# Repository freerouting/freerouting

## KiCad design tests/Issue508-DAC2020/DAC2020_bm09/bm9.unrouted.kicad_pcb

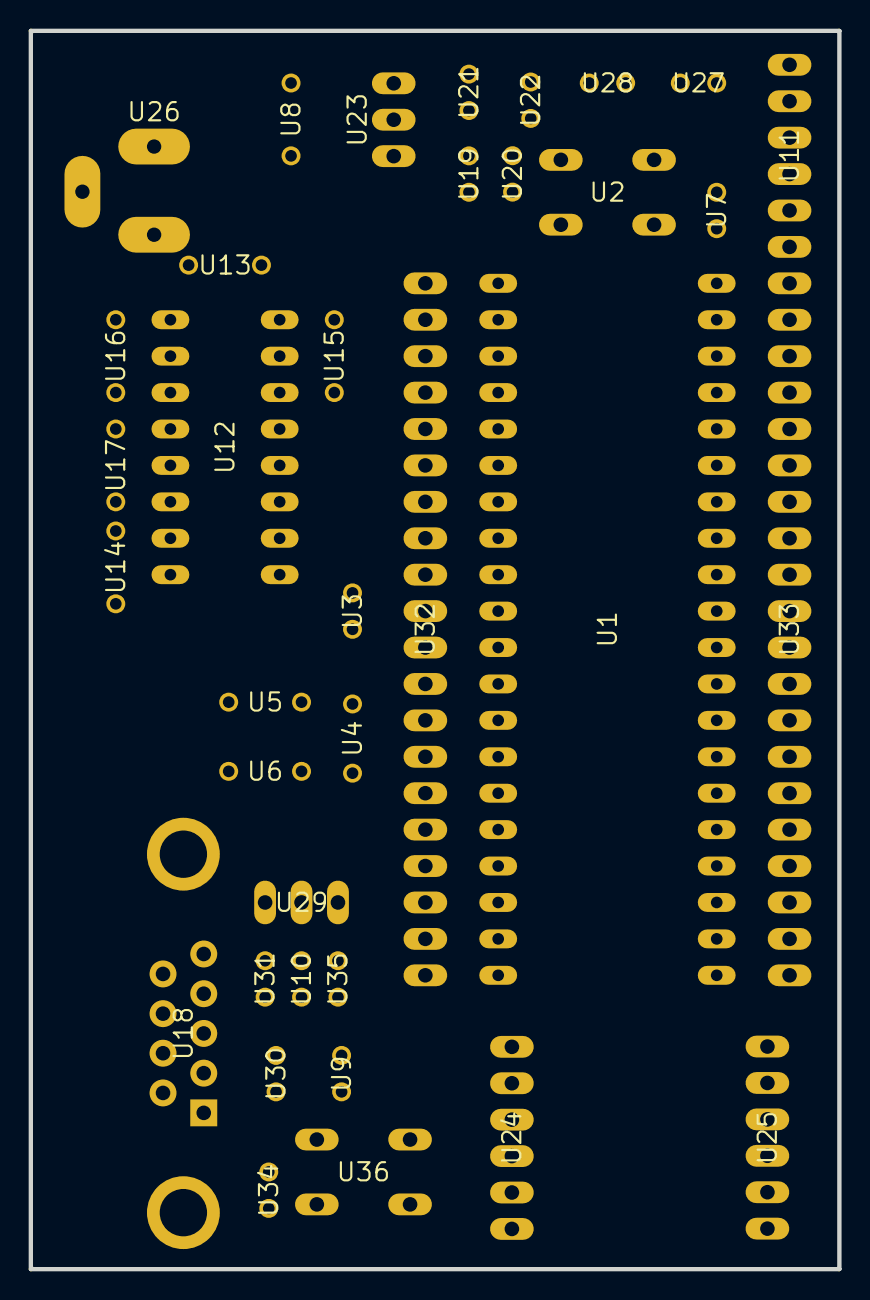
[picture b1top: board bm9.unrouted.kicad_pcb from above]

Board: 16 copper layers, 56.4 x 86.4 mm, 36 parts (0 on the bottom side), 58 nets, no tracks yet.

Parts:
U1: DIL40
U2, U36: B3F-10XX
U3, U22: C025-024X044
U4: HC49_S
U5, U6, U13, U14, U15, U16, U17: C050-024X044
U7, U10, U19, U20, U21, U28, U31, U34, U35: V526-0
U8: C050-025X075
U9, U27, U30: LED3MM
U11, U24, U25: 1X06
U12: DIL16
U18: DB9
U23: 317TS
U26: 733980-62
U29: MA03-1
U32, U33: MA20-1

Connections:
/3.3V_SRC: U1.11, U1.32, U3.1, U7.1, U11.2, U12.16, U13.2, U15.1, U21.2, U22.1, U23.2, U24.3, U28.1, U32.10, U33.9, U36.1
/MRF_CS: U1.17, U24.5, U32.4
/MRF_INT: U1.34, U25.3, U33.7
/MRF_RESET: U1.15, U25.5, U32.6
/MRF_SCK: U1.18, U25.1, U32.3
/MRF_SDI: U1.23, U24.6, U33.18
/MRF_SDO: U1.24, U25.2, U33.17
/MRF_WAKE: U1.16, U25.4, U32.5
/N$17: U1.26, U12.9, U33.15
/N$21: U1.25, U12.10, U33.16
/OS1: U1.13, U4.1, U5.1, U32.8
/OSC2: U1.14, U4.2, U6.1, U32.7
GND: U1.12, U1.31, U2.1, U3.2, U5.2, U6.2, U8.2, U9.K, U11.3, U12.15, U14.1, U15.2, U18.5, U20.1, U22.2, U24.1, U24.2, U25.6, U26.1, U27.K, U30.K, U32.9, U33.10, U34.2
unnamed: U12.2, U13.1
unnamed: U12.6, U14.2
unnamed: U12.1, U16.1
unnamed: U12.3, U16.2
unnamed: U12.4, U17.1
unnamed: U12.5, U17.2
unnamed: U8.1, U23.3, U26.2
unnamed: U12.7, U18.2
unnamed: U12.8, U18.3
unnamed: U1.1, U2.3, U7.2, U11.1, U32.20
unnamed: U1.2, U32.19
unnamed: U1.3, U32.18
unnamed: U1.4, U32.17
unnamed: U1.5, U32.16
unnamed: U1.6, U32.15
unnamed: U1.7, U32.14
unnamed: U1.8, U32.13
unnamed: U1.9, U32.12
unnamed: U1.10, U32.11
unnamed: U1.19, U32.2
unnamed: U1.20, U32.1
unnamed: U1.21, U33.20
unnamed: U1.22, U33.19
unnamed: U1.27, U33.14
unnamed: U1.28, U33.13
unnamed: U1.29, U33.12
unnamed: U1.30, U33.11
unnamed: U1.33, U33.8
unnamed: U1.35, U33.6
unnamed: U1.36, U33.5
unnamed: U1.37, U33.4
unnamed: U1.38, U33.3
unnamed: U1.39, U11.5, U33.2
unnamed: U1.40, U11.4, U33.1
unnamed: U19.2, U21.1, U23.1
unnamed: U27.A, U28.2
unnamed: U30.A, U31.2
unnamed: U9.A, U10.2
unnamed: U34.1, U35.2, U36.3
unnamed: U29.3, U35.1
unnamed: U10.1, U29.2
unnamed: U29.1, U31.1
unnamed: U19.1, U20.2
unnamed: U18.1, U18.4, U18.6
unnamed: U18.7, U18.8

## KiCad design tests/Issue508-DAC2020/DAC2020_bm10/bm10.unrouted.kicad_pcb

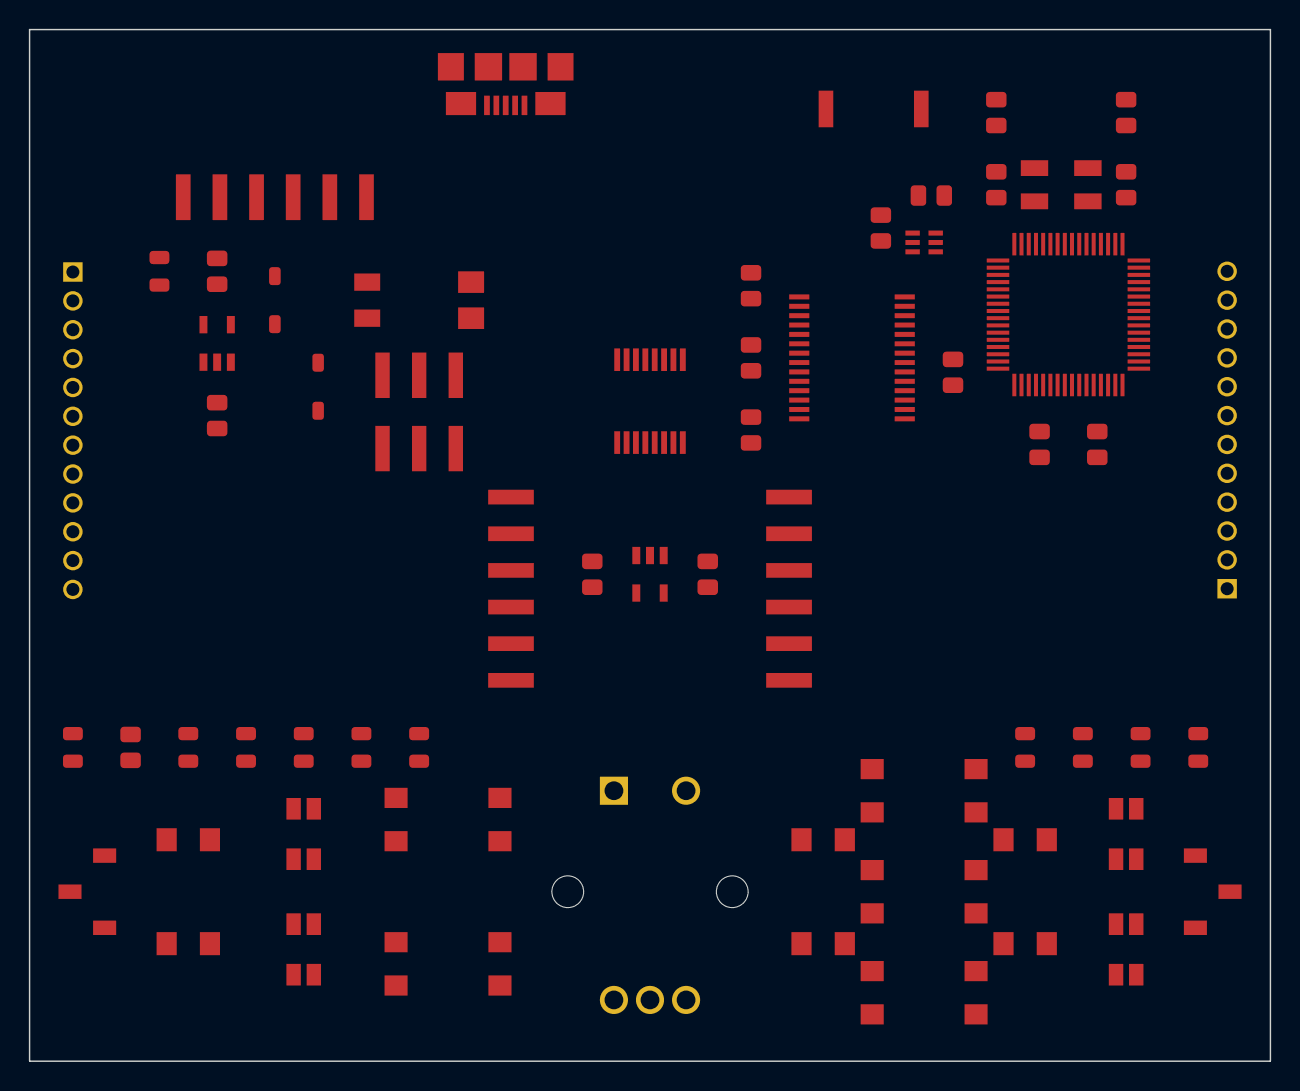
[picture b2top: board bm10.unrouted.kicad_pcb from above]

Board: 4 copper layers, 86.0 x 71.5 mm, 61 parts (0 on the bottom side), 63 nets, no tracks yet.

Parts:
A1: ANTENNA-CHIP; ANT-2.4GHZ-6.5X2.2MM
B1, B4, B5, B6, B7, B8, B9, B10: PUSHBUTTON_-4.5X4.5; 4.5MM_TACTILE_SWITCH_TL3305AF160QG
B2: BALUN0805; BALUN
B3: BATTERY-SPRING-SMD; WIRE-TERMINAL-1X2-2.5MM-SMD-AVX-009276002021106
C1, C8, C9: 0.1uF; CAPC2012X140_HS
C2: 0.75pF; CAPC2012X140_HS
C3: 22pF; CAPC2012X140_HS
C4, C10, C11, C12, C13, C16, C17: 1uF; CAPC2012X140_HS
C5, C6, C7: 10uF; CAPC2012X140_HS
C14, C15: 12pF; CAPC2012X140_HS
D1, D4, D5, D6: LED-2X-GREEN_RED; LED-2X-LTST-C155
D2, D3: 360mV; SOD3716X135_HS
E1: ROTARY-ENCODER-W_BUTTON-BOURNS-PEC12R-4217F; BOURNS-PEC12R
J1: USB-MICROA-AMPHENOL-10118192-0001LF; USB-MICROA-10118192-0001LF
J2, J3: 2.4K; JST-13-PTH
J4: AVR_SPI_PRG_6-SMD; 2X3-SMD
J7, J8: FRSKY-GIMBAL-2X-SERVO-SMD; 2X-SERVO-SMD
JP1: FTDI_BASIC-SMD; FTDI-BASIC-SMD
R1, R3, R13, R14, R15, R16, R17, R18: 510; RESC2012X60_HS
R2: 10K; RESC2012X60_HS
R7: 2.2K; RESC2012X60_HS
R8: 1.2K; RESC2012X60_HS
S1, S2: POWER-SWITCH-MFS201N-9-Z-SMD-VERTICAL; JS102011JCQN
U1: 3.3V; SOT23-DBV
U2: MCP73831T-2ACI/OT; SOT23-5
U3: FT232RLSSOP; SSOP28DB
U4: ATMEGA128RFA1; QFN-64
U5: DPDT-X2; SOP65P640X110-16
Y1: CRYSTAL5X3; CRYSTAL-SMD-5X3

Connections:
3V3: C12.1, C16.1, C17.1, D4.A2, J4.2, JP1.VCC, R2.2, R8.2, R13.2, R14.2, S2.1, U1.5, U4.23, U4.34, U4.44, U4.54, U4.59, U5.16
/BTN1/SCL: B4.3, B4.4, U4.25
/BTN2/SDA: B5.3, B5.4, U4.26
/BTN_CENTER: B9.1, B9.2, U4.53
/BTN_DOWN: B10.1, B10.2, U4.28
/BTN_LEFT: B7.1, B7.2, U4.51
/BTN_RIGHT: B8.1, B8.2, U4.52
/BTN_UP: B6.1, B6.2, U4.50
/CTS: U3.11, U5.2
/CTS-1: JP1.CTS, U5.1
/DTR: U3.2, U5.14
/DTR-0: C1.2, U5.15
/DTR-1: JP1.DTR, U5.13
/E1-A: E1.A, U4.40
/E1-B: E1.B, U4.41
/E1-BUT: E1.BUTA, U4.27
/FTDI_OUT: C4.2, C9.1, U3.4, U3.17
/GREF: J2.1, J2.4, J3.1, J3.4, J7.1, J7.4, J8.1, J8.4, R8.1
/MISO: J4.1, U4.39
/MOSI: J4.4, U4.38
/PITCH: J3.V, J8.V, U4.2
/RESET: B1.1, B1.2, C1.1, J4.5, R2.1, U4.12
/RF: D4.A1, U4.16
/ROLL: J3.H, J8.H, U4.1
/RXI: U3.5, U5.10
/RXI-0: U4.47, U5.11
/RXI-1: JP1.RXI, U5.9
/RXLED: D5.C2, U3.22
/SCK: J4.3, U4.37
/THROTTLE: J2.V, J7.V, U4.64
/TXLED: D5.C1, U3.23
/TXO: U3.1, U5.6
/TXO-0: U4.46, U5.7
/TXO-1: JP1.TXO, U5.5
/USB_D_N: J1.2, U3.16
/USB_D_P: J1.3, U3.15
/VBUS: C5.1, D1.A2, D2.A, J1.1, U2.4
/VREG_IN: C7.1, C8.1, C10.1, S1.1, U1.1, U1.3, U3.20
/YAW: J2.H, J7.H, U4.63
GND: B1.3, B1.4, B2.5, B3.2A, B3.2B, B4.1, B4.2, B5.1, B5.2, B6.3, B6.4, B7.3, B7.4, B8.3, B8.4, B9.3, B9.4, B10.3, B10.4, C2.2, C3.1, C4.1, C5.2, C6.2, C7.2, C8.2, C9.2, C10.2, C11.2, C12.2, C13.2, C14.2, C15.2, C16.2, C17.2, D1.C1, E1.BUTB, E1.C, J1.5, J1.6, J1.7, J1.8, J1.9, J1.10, J1.11, J2.3, J2.6, J3.3, J3.6, J4.6, J7.3, J7.6, J8.3, J8.6, JP1.GND, R7.2, R15.1, R16.1, R17.1, R18.1, S2.3, U1.2, U2.2, U3.7, U3.18, U3.21, U3.25, U3.26, U4.7, U4.10, U4.11, U4.20, U4.24, U4.33, U4.35, U4.45, U4.55, U4.58, U4.61, U5.8
unnamed: A1.FEED, B2.1, C2.1
unnamed: B2.2, C3.2
unnamed: B2.3, U4.9
unnamed: B2.4, U4.8
unnamed: B3.1A, B3.1B, C6.1, D3.A, U2.3
unnamed: C11.1, U4.21, U4.22
unnamed: C13.1, U4.60
unnamed: C14.1, U4.57, Y1.3
unnamed: C15.1, U4.56, Y1.1
unnamed: D1.A1, R3.1
unnamed: D1.C2, R1.1
unnamed: D4.C1, R15.2
unnamed: D4.C2, R16.2
unnamed: D5.A1, R14.1
unnamed: D5.A2, R13.1
unnamed: D6.A1, U4.15
unnamed: D6.A2, U4.14
unnamed: D6.C1, R18.2
unnamed: D6.C2, R17.2
unnamed: R1.2, R3.2, U2.1
unnamed: R7.1, U2.5
unnamed: S2.2, U5.4, U5.12
VBAT: D2.C, D3.C, S1.2

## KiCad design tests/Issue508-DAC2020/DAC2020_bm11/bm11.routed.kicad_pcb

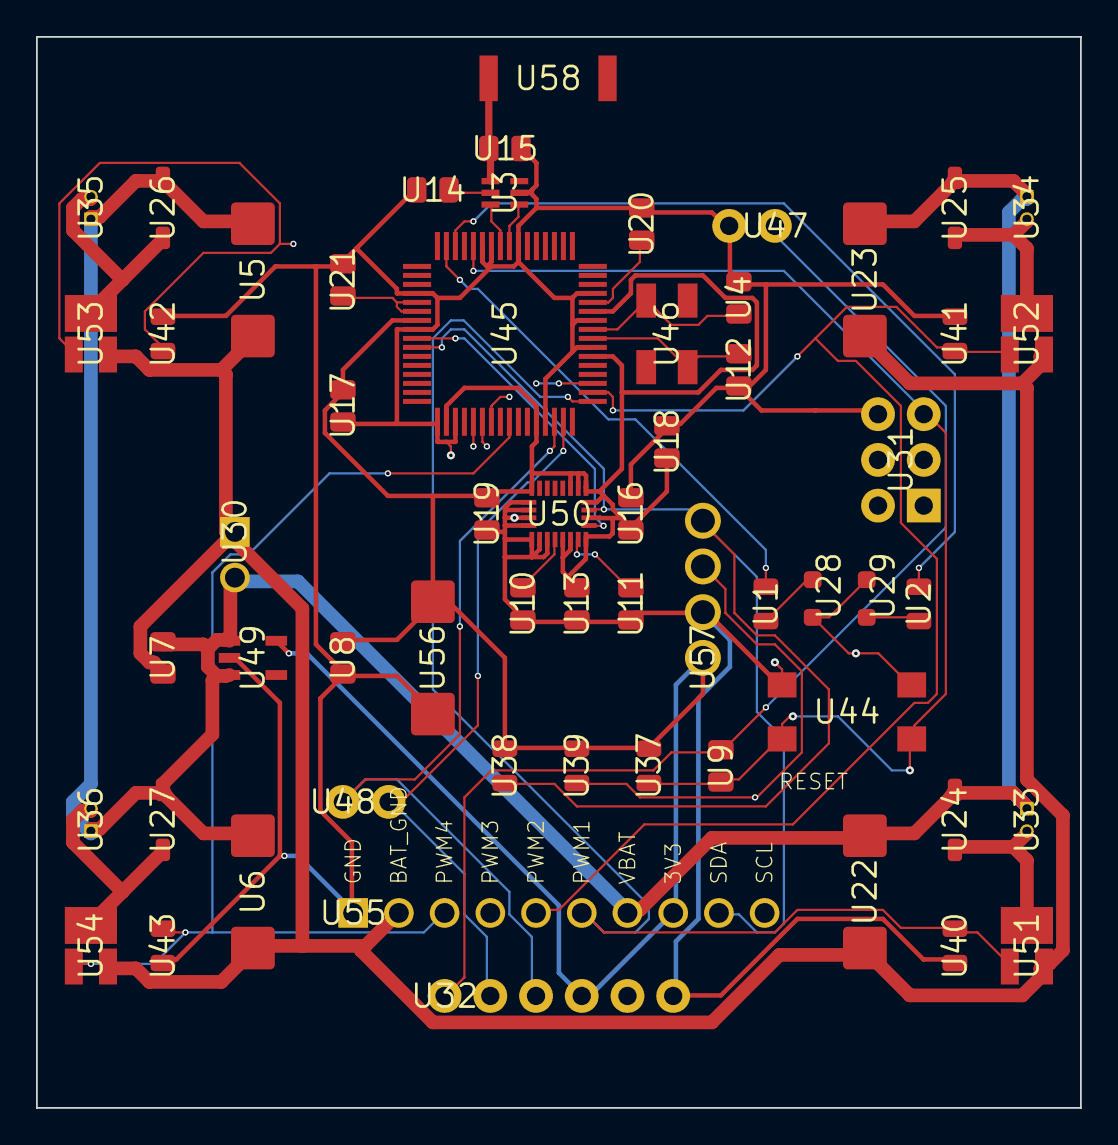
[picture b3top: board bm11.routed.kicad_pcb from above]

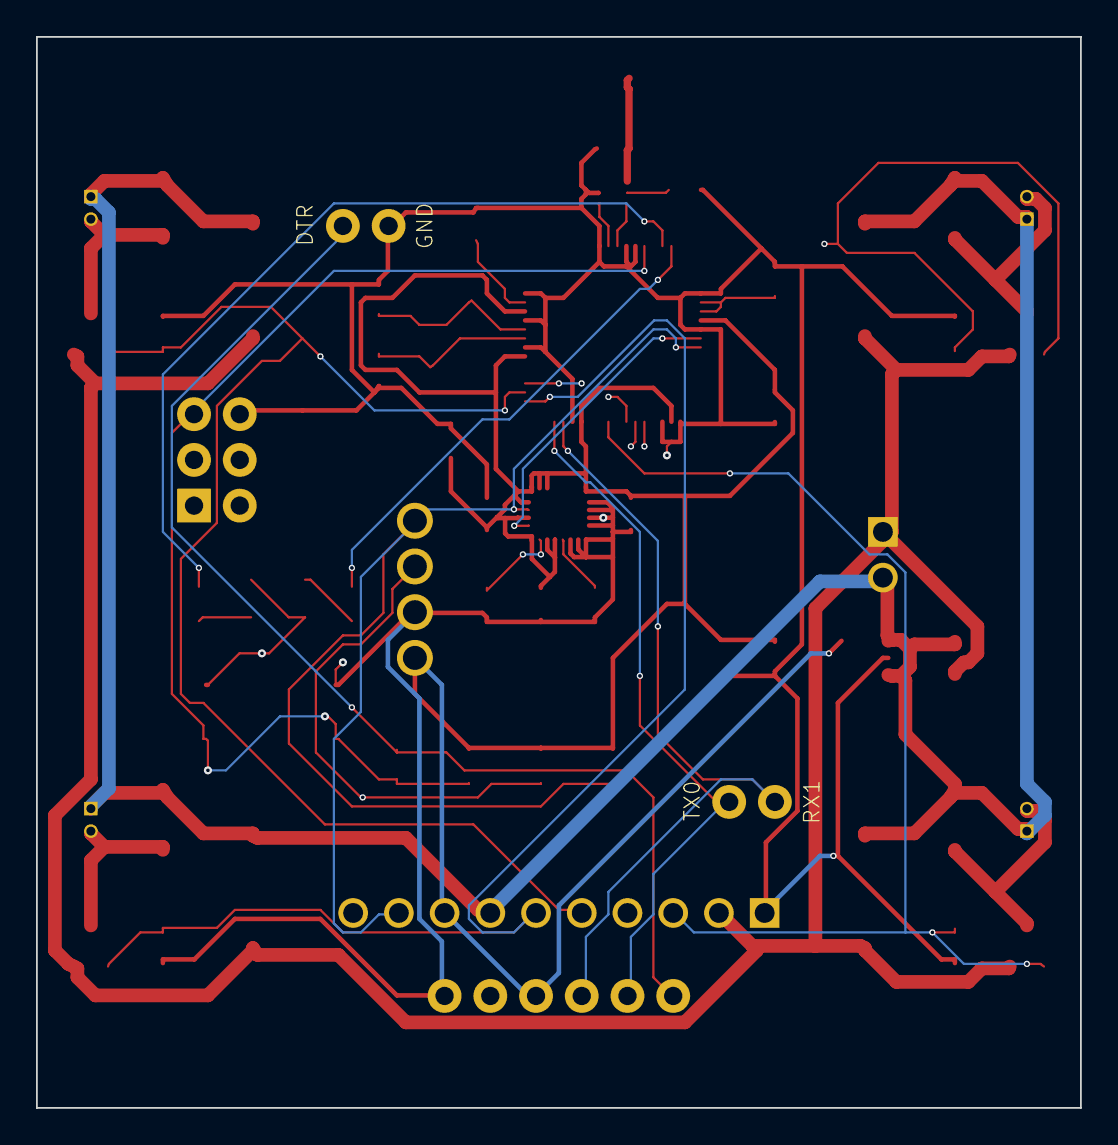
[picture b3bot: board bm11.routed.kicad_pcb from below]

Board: 4 copper layers, 58.0 x 59.5 mm, 58 parts (2 on the bottom side), 35 nets.

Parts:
U1, U2, U37, U38, U39, U40, U41, U42, U43: RESC2012X60_HS
U3: BALUN
U4, U7, U8, U9, U10, U11, U12, U13, U14, U15, U16, U17, U18, U19, U20, U21: CAPC2012X140_HS
U5, U6, U22, U23, U56: CAPMP7343X310_HS
U24, U25, U26, U27: SOD3716X135_HS
U28, U29: LEDSC125X200X120-2_HS
U30: MALE_HEADER_2X1_0.1IN
U31: 2X3-NS
U32: FTDI_BASIC
U33, U34, U35, U36: MOLEX-0530470210
U44: 4.5MM_TACTILE_SWITCH_TL3305AF160QG
U45: QFN-64
U46: CRYSTAL-SMD-5X3
U47: FTDI_BASIC_2PIN_2
U48: FTDI_BASIC_2PIN_1
U49: SOT23-DBV
U50: NEW_IMU_MEDIUM
U51, U52, U53, U54: N_FET_SI2302CDS-T1-E3CT-ND
U55: HDRV10W63P254_10X1_2540X254H838_HS
U57: HDRVR4W80P254_1X4_1066X254X850B
U58: ANT-2.4GHZ-6.5X2.2MM

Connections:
3V3: U8.1, U13.1, U16.1, U17.1, U18.1, U19.1, U32.VCC, U37.2, U38.2, U39.2, U45.23, U45.34, U45.44, U45.54, U45.59, U49.5, U50.CS_A/G, U50.CS_M, U50.DEN_A/G, U50.SDO_A/G, U50.SDO_M, U50.VDD1, U50.VDD2, U50.VDDIO, U50.VDDIO2, U55.8, U56.1, U57.1
/DTR: U9.1, U32.DTR, U47.DTR
/LED1: U2.2, U45.14
/LED2: U1.2, U45.15
/MISO: U31.1, U45.39
/MOSI: U31.4, U45.38
/PWM1: U40.1, U45.49, U51.G, U55.6
/PWM2: U41.1, U45.50, U52.G, U55.5
/PWM3: U42.1, U45.51, U53.G, U55.4
/PWM4: U43.1, U45.41, U54.G, U55.3
/RESET: U9.2, U31.5, U37.1, U44.3, U44.4, U45.12
/RX0: U32.TXO, U45.46, U48.TXO
/SCK: U31.3, U45.37
/SCL: U39.1, U45.25, U50.SCL/SPC, U55.10, U57.3
/SDA: U38.1, U45.26, U50.SDA/SDI/SDO, U55.9, U57.4
/TX0: U32.RXI, U45.47, U48.RXI
BAT_GND: U5.2, U6.2, U7.2, U22.2, U23.2, U30.1, U51.S, U52.S, U53.S, U54.S, U55.2
GND: U3.5, U4.2, U8.2, U10.2, U11.2, U12.2, U13.2, U14.2, U15.2, U16.2, U17.2, U18.2, U19.2, U20.2, U21.2, U28.2, U29.1, U31.6, U32.GND, U40.2, U41.2, U42.2, U43.2, U44.1, U44.2, U45.7, U45.10, U45.11, U45.20, U45.24, U45.33, U45.35, U45.45, U45.55, U45.58, U45.61, U47.CTS, U49.2, U50.GND1, U50.GND2, U50.RES1, U50.RES2, U50.RES3, U50.RES4, U50.RES5, U55.1, U56.2, U57.2
unnamed: U3.1, U15.1, U58.FEED
unnamed: U3.2, U14.1
unnamed: U3.3, U45.9
unnamed: U3.4, U45.8
unnamed: U4.1, U45.57, U46.1
unnamed: U12.1, U45.56, U46.3
unnamed: U20.1, U45.60
unnamed: U21.1, U45.21, U45.22
unnamed: U10.1, U50.CAP
unnamed: U11.1, U50.C1
unnamed: U24.A, U33.2, U51.D
unnamed: U25.A, U34.2, U52.D
unnamed: U26.A, U35.2, U53.D
unnamed: U27.A, U36.2, U54.D
unnamed: U1.1, U28.1
unnamed: U2.1, U29.2
VBAT: U5.1, U6.1, U7.1, U22.1, U23.1, U24.C, U25.C, U26.C, U27.C, U30.2, U33.1, U34.1, U35.1, U36.1, U49.1, U49.3, U55.7

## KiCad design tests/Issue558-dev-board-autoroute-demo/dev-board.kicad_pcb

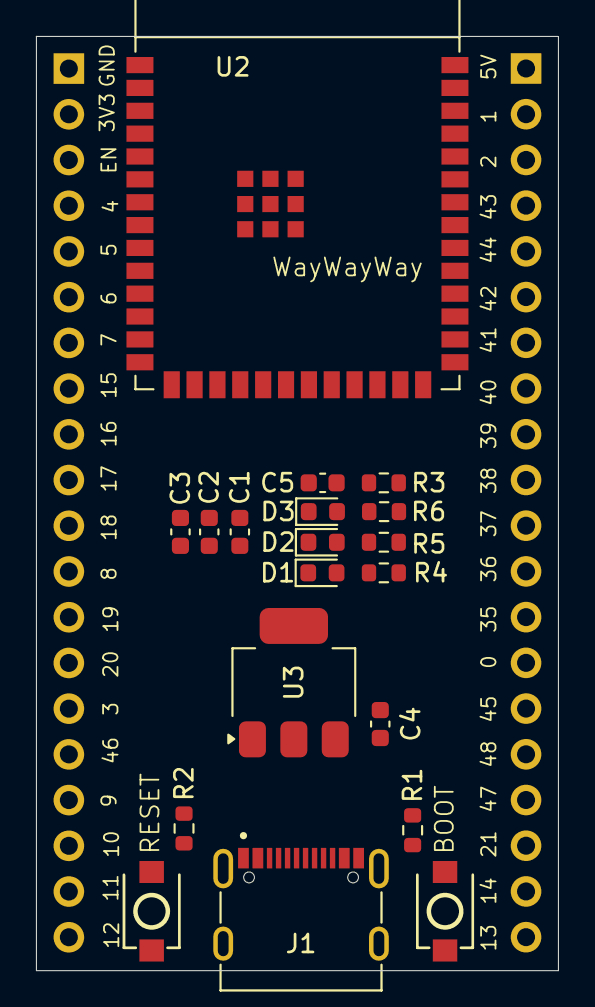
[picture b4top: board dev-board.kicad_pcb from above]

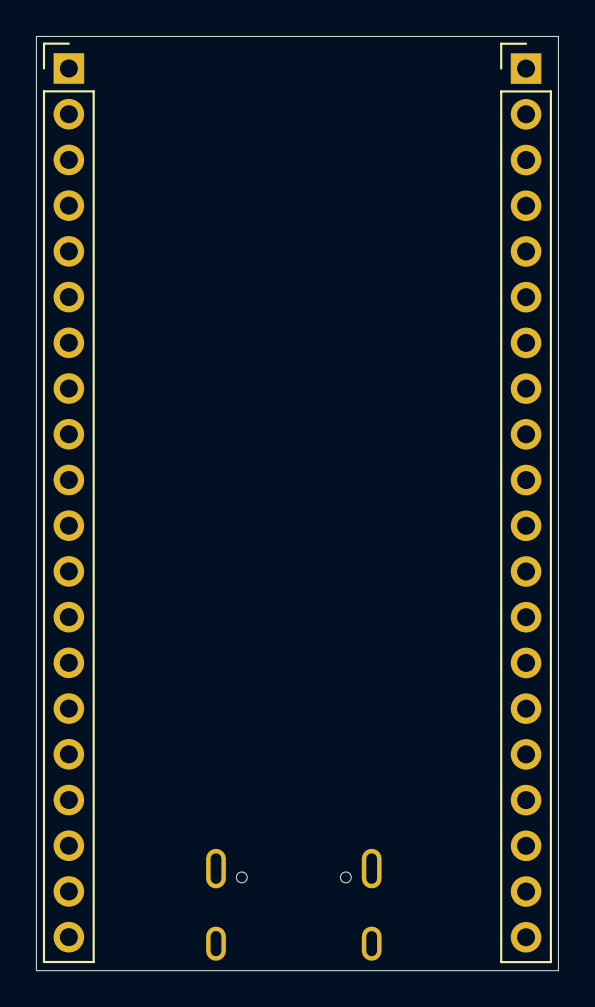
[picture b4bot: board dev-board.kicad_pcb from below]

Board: 2 copper layers, 29.0 x 51.9 mm, 21 parts (2 on the bottom side), 45 nets, no tracks yet.

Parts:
C1, C4, C5: 10u; C_0603_1608Metric
C2: 22u; C_0603_1608Metric
C3: 100n; C_0603_1608Metric
D1: RED; LED_0603_1608Metric
D2: GREEN; LED_0603_1608Metric
D3: BLUE; LED_0603_1608Metric
J1: TYPE-C-31-M-12; HRO_TYPE-C-31-M-12
J2, J3: Conn_01x20_Pin; PinHeader_1x20_P2.54mm_Vertical
R1, R2, R3, R4, R5, R6: 5.1K; R_0603_1608Metric
SW1, SW2: TS-1088-AR02016; SW-SMD_L3.9-W3.0-P4.45
U2: ESP32-S3-WROOM-1
U3: LD1117S33TR_SOT223; SOT-223-3_TabPin2

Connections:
+3V3: C1.1, C2.1, C3.1, J2.2, R3.1, R5.1, U2.2 (3V3), U3.2 (VO)
+5V: C4.1, J1.A4_B9 (VBUS), J1.B4_A9 (VBUS), J3.1, R4.1, U3.3 (VI)
D+: J1.A6 (DP1), J1.B6 (DP2), J2.14, U2.14 (GPIO20/U1CTS/ADC2_CH9/CLK_OUT1/USB_D+)
D-: J1.A7 (DN1), J1.B7 (DN2), J2.13, U2.13 (GPIO19/U1RTS/ADC2_CH8/CLK_OUT2/USB_D-)
EN: C5.1, J2.3, R3.2, SW1.2, U2.3 (EN)
GND: C1.2, C2.2, C3.2, C4.2, C5.2, D1.1 (K), D2.1 (K), D3.1 (K), J1.A1_B12 (GND), J1.B1_A12 (GND), J1.S1 (SHIELD), J1.S2 (SHIELD), J1.S3 (SHIELD), J1.S4 (SHIELD), J2.1, R1.2, R2.2, SW1.1, SW2.1, U2.1 (GND), U2.40 (GND), U2.41 (GND), U3.1 (GND)
GPIO0: J3.14, SW2.2, U2.27 (GPIO0/BOOT)
GPIO1: J3.2, U2.39 (GPIO1/TOUCH1/ADC1_CH0)
GPIO2: J3.3, U2.38 (GPIO2/TOUCH2/ADC1_CH1)
GPIO3: J2.15, U2.15 (GPIO3/TOUCH3/ADC1_CH2)
GPIO4: J2.4, U2.4 (GPIO4/TOUCH4/ADC1_CH3)
GPIO5: J2.5, U2.5 (GPIO5/TOUCH5/ADC1_CH4)
GPIO6: J2.6, U2.6 (GPIO6/TOUCH6/ADC1_CH5)
GPIO7: J2.7, U2.7 (GPIO7/TOUCH7/ADC1_CH6)
GPIO8: J2.12, U2.12 (GPIO8/TOUCH8/ADC1_CH7/SUBSPICS1)
GPIO9: J2.17, U2.17 (GPIO9/TOUCH9/ADC1_CH8/FSPIHD/SUBSPIHD)
GPIO10: J2.18, U2.18 (GPIO10/TOUCH10/ADC1_CH9/FSPICS0/FSPIIO4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)
GPIO11: J2.19, U2.19 (GPIO11/TOUCH11/ADC2_CH0/FSPID/FSPIIO5/S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)
GPIO12: J2.20, U2.20 (GPIO12/TOUCH12/ADC2_CH1/FSPICLK/FSPIIO6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)
GPIO13: J3.20, U2.21 (GPIO13/TOUCH13/ADC2_CH2/FSPIQ/FSPIIO7/S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)
GPIO14: J3.19, U2.22 (GPIO14/TOUCH14/ADC2_CH3/FSPIWP/FSPIDQS/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)
GPIO15: J2.8, U2.8 (GPIO15/U0RTS/ADC2_CH4/XTAL_32K_P)
GPIO16: J2.9, U2.9 (GPIO16/U0CTS/ADC2_CH5/XTAL_32K_N)
GPIO17: J2.10, U2.10 (GPIO17/U1TXD/ADC2_CH6)
GPIO18: J2.11, U2.11 (GPIO18/U1RXD/ADC2_CH7/CLK_OUT3)
GPIO21: J3.18, R6.1, U2.23 (GPIO21)
GPIO35: J3.13, U2.28 (SPIIO6/GPIO35/FSPID/SUBSPID)
GPIO36: J3.12, U2.29 (SPIIO7/GPIO36/FSPICLK/SUBSPICLK)
GPIO37: J3.11, U2.30 (SPIDQS/GPIO37/FSPIQ/SUBSPIQ)
GPIO38: J3.10, U2.31 (GPIO38/FSPIWP/SUBSPIWP)
GPIO39: J3.9, U2.32 (MTCK/GPIO39/CLK_OUT3/SUBSPICS1)
GPIO40: J3.8, U2.33 (MTDO/GPIO40/CLK_OUT2)
GPIO41: J3.7, U2.34 (MTDI/GPIO41/CLK_OUT1)
GPIO42: J3.6, U2.35 (MTMS/GPIO42)
GPIO43: J3.4, U2.37 (U0TXD/GPIO43/CLK_OUT1)
GPIO44: J3.5, U2.36 (U0RXD/GPIO44/CLK_OUT2)
GPIO45: J3.15, U2.26 (GPIO45)
GPIO46: J2.16, U2.16 (GPIO46)
GPIO47: J3.17, U2.24 (GPIO47/SPICLK_P/SUBSPICLK_P_DIFF)
GPIO48: J3.16, U2.25 (GPIO48/SPICLK_N/SUBSPICLK_N_DIFF)
unnamed: D1.2 (A), R4.2
unnamed: D2.2 (A), R5.2
unnamed: D3.2 (A), R6.2
unnamed: J1.A5 (CC1), R2.1
unnamed: J1.B5 (CC2), R1.1

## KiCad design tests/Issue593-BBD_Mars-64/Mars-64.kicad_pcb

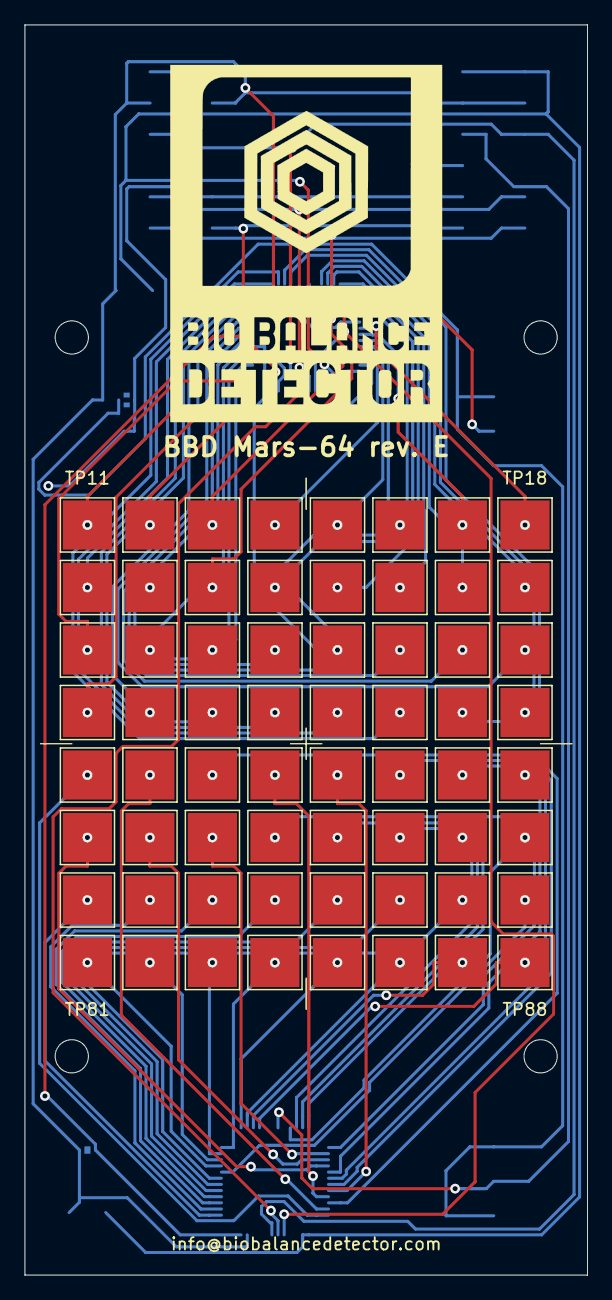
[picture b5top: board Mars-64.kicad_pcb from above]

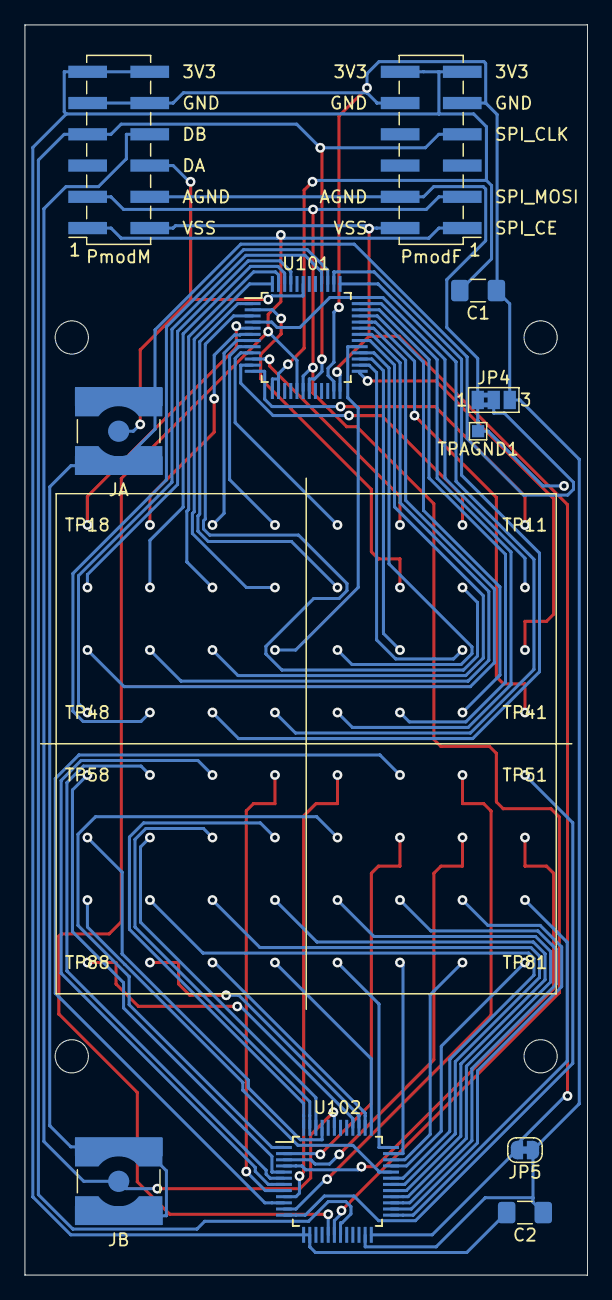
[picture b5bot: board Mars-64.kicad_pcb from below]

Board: 4 copper layers, 45.7 x 101.6 mm, 79 parts (11 on the bottom side), 74 nets.

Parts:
C1, C2: 100 nF; C_1206_3216Metric_Pad1.42x1.75mm_HandSolder
H1, H2, H3, H4: MountingHole; MountingHole_2.7mm_M2.5
JA: Conn_Coaxial; SMA_Amphenol_132134-10_Vertical
JB: Conn_Coaxial; SMA_Amphenol_132134-10_Vertical
JP4: Jumper_NC_Dual; SolderJumper-3_P1.3mm_Bridged2Bar12_Pad1.0x1.5mm_NumberLabe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
JP5: SolderJumper_2_Bridged; SolderJumper-2_P1.3mm_Bridged_RoundedPad1.0x1.5mm
PmodF: Conn_02x06_Top_Bottom; PinHeader_2x06_P2.54mm_Vertical_SMD_TopBottom
PmodM: Conn_02x06_Top_Bottom; PinHeader_2x06_P2.54mm_Vertical_SMD_TopBottom_Mirrored
TP101, TP102, TP103, TP104, TP105, TP106, TP107, TP108, TP109, TP110, TP111, TP112, TP113, TP114, TP115, TP116, TP117, TP118, TP119, TP120, TP121, TP122, TP123, TP124, TP125, TP126, TP127, TP128, TP129, TP130, TP131, TP132, TP201, TP202, TP203, TP204, TP205, TP206, TP207, TP208, TP209, TP210, TP211, TP212, TP213, TP214, TP215, TP216, TP217, TP218, TP219, TP220, TP221, TP222, TP223, TP224, TP225, TP226, TP227, TP228, TP229, TP230, TP231, TP232: TestPoint_Small; TestPoint_Pad_4.0x4.0mm
TPAGND1: TestPoint_Small; TestPoint_Pad_1.0x1.0mm
U101, U102: ADG731; TQFP-48_7x7mm_P0.5mm

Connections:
/AGND: JP4.1, PmodF.8, PmodM.8, TPAGND1.1
/DA: JA.1, PmodM.9, U101.43
/DB: JB.1, PmodM.10, U102.43
/SPI_CLK: PmodF.4, PmodM.4, U101.19, U102.19
/SPI_MOSI: PmodF.2, PmodM.2, U101.18, U102.18
/VCC3V3: C1.2, C2.2, PmodF.6, PmodF.12, PmodM.6, PmodM.12, U101.13, U101.14, U102.13, U102.14
/VSS: JP5.2, PmodF.7, PmodM.7, U101.24, U102.24
/~SPI_CE: PmodF.1, PmodM.1, U101.17, U102.17
GND: C1.1, C2.1, JP4.3, JP5.1, PmodF.5, PmodF.11, PmodM.5, PmodM.11, U101.23, U102.23
unnamed: JA.2, JB.2, JP4.2
unnamed: TP101.1, U101.12
unnamed: TP102.1, U101.11
unnamed: TP103.1, U101.10
unnamed: TP104.1, U101.9
unnamed: TP105.1, U101.8
unnamed: TP106.1, U101.7
unnamed: TP107.1, U101.6
unnamed: TP108.1, U101.5
unnamed: TP109.1, U101.4
unnamed: TP110.1, U101.3
unnamed: TP111.1, U101.2
unnamed: TP112.1, U101.1
unnamed: TP113.1, U101.48
unnamed: TP114.1, U101.47
unnamed: TP115.1, U101.46
unnamed: TP116.1, U101.45
unnamed: TP117.1, U101.25
unnamed: TP118.1, U101.26
unnamed: TP119.1, U101.27
unnamed: TP120.1, U101.28
unnamed: TP121.1, U101.29
unnamed: TP122.1, U101.30
unnamed: TP123.1, U101.31
unnamed: TP124.1, U101.32
unnamed: TP125.1, U101.33
unnamed: TP126.1, U101.34
unnamed: TP127.1, U101.35
unnamed: TP128.1, U101.36
unnamed: TP129.1, U101.37
unnamed: TP130.1, U101.38
unnamed: TP131.1, U101.39
unnamed: TP132.1, U101.40
unnamed: TP201.1, U102.12
unnamed: TP202.1, U102.11
unnamed: TP203.1, U102.10
unnamed: TP204.1, U102.9
unnamed: TP205.1, U102.8
unnamed: TP206.1, U102.7
unnamed: TP207.1, U102.6
unnamed: TP208.1, U102.5
unnamed: TP209.1, U102.4
unnamed: TP210.1, U102.3
unnamed: TP211.1, U102.2
unnamed: TP212.1, U102.1
unnamed: TP213.1, U102.48
unnamed: TP214.1, U102.47
unnamed: TP215.1, U102.46
unnamed: TP216.1, U102.45
unnamed: TP217.1, U102.25
unnamed: TP218.1, U102.26
unnamed: TP219.1, U102.27
unnamed: TP220.1, U102.28
unnamed: TP221.1, U102.29
unnamed: TP222.1, U102.30
unnamed: TP223.1, U102.31
unnamed: TP224.1, U102.32
unnamed: TP225.1, U102.33
unnamed: TP226.1, U102.34
unnamed: TP227.1, U102.35
unnamed: TP228.1, U102.36
unnamed: TP229.1, U102.37
unnamed: TP230.1, U102.38
unnamed: TP231.1, U102.39
unnamed: TP232.1, U102.40
